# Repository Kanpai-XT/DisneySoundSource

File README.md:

# DisneySoundSource
A simple Disney Sound Source (DSS) clone based on schematics by shock__ using a CVX4 DAC by dreamblaster for audio output. The DSS provides audio out over the parallel port for a handful of games. Regardless of the CVX circuits, this device is not compatible with a Covox Speech Thing.

## Files
This repository contains the following files:
- shock__ &nbsp;&nbsp;&nbsp;&nbsp; &nbsp;&nbsp;&nbsp;&nbsp; &nbsp;&nbsp;&nbsp;&nbsp; &nbsp;&nbsp;&nbsp;&nbsp; &nbsp;&nbsp;&nbsp; subfolder conataining the original files
- dss_smd.brd &nbsp;&nbsp;&nbsp;&nbsp; &nbsp;&nbsp;&nbsp;&nbsp; &nbsp;&nbsp;&nbsp;&nbsp; &nbsp; Autodesk Eagle board file
- dd_smd.sch &nbsp;&nbsp;&nbsp;&nbsp; &nbsp;&nbsp;&nbsp;&nbsp; &nbsp;&nbsp;&nbsp;&nbsp; &nbsp;&nbsp; Autodesk Eagle schematics file
- dds_smd_bom.csv &nbsp;&nbsp;&nbsp;&nbsp; &nbsp;&nbsp; bill of materials
- dds_smd_gerber.zip &nbsp;&nbsp;&nbsp;&nbsp; Gerber files
- NE555N.ods &nbsp;&nbsp;&nbsp;&nbsp; &nbsp;&nbsp;&nbsp;&nbsp; &nbsp;&nbsp;&nbsp;&nbsp; &nbsp; spreadsheet to calculate the resistance of the trimmer R10 for a 7kHz signal 
- license.md &nbsp;&nbsp;&nbsp;&nbsp; &nbsp;&nbsp;&nbsp;&nbsp; &nbsp;&nbsp;&nbsp;&nbsp; &nbsp;&nbsp;&nbsp;&nbsp; CC-BY-NC-SA

## Gerber Files
This repository includes gerber files for PCB manufacturing. However, this PCB has plated slotted holes for the audio jack and usb jack. You are adviced to notify the manufacturer about these plated slotted holes! 

## Credits
- shock__ for the schematics and Eagle files.
- dreamblaster and Scali from VOGONS forum, for the CVX4.
- Jepael from VOGONS forum, for his input and checking over the original schematics by shock__.
- keropi from VOGONS forum, for supplying photos and measuring parts on his original DSS.
- x1541 from Verein zum Erhalt klassischer Computer e.V. (club for the preservation of classic computers) for suggesting the cheaper and non-discontinued CD40105 FIFOs.
- matze79 from DOSReloaded, for additonal circuits on the power supply.

## License
>CC-BY-NC-SA - basically do with it what you want, as long as you credit me, don't offer it commercially and make your extensions/derivates available under the same license. Only exception, you're allowed to sell PCBs created/derived from this package at a price that covers your expenses but doesn't earn you any money (I guess a $ for handling is only fair, but selling a $3 PCB for $30 would be a scumbag move and in violation of the license).

by shock__

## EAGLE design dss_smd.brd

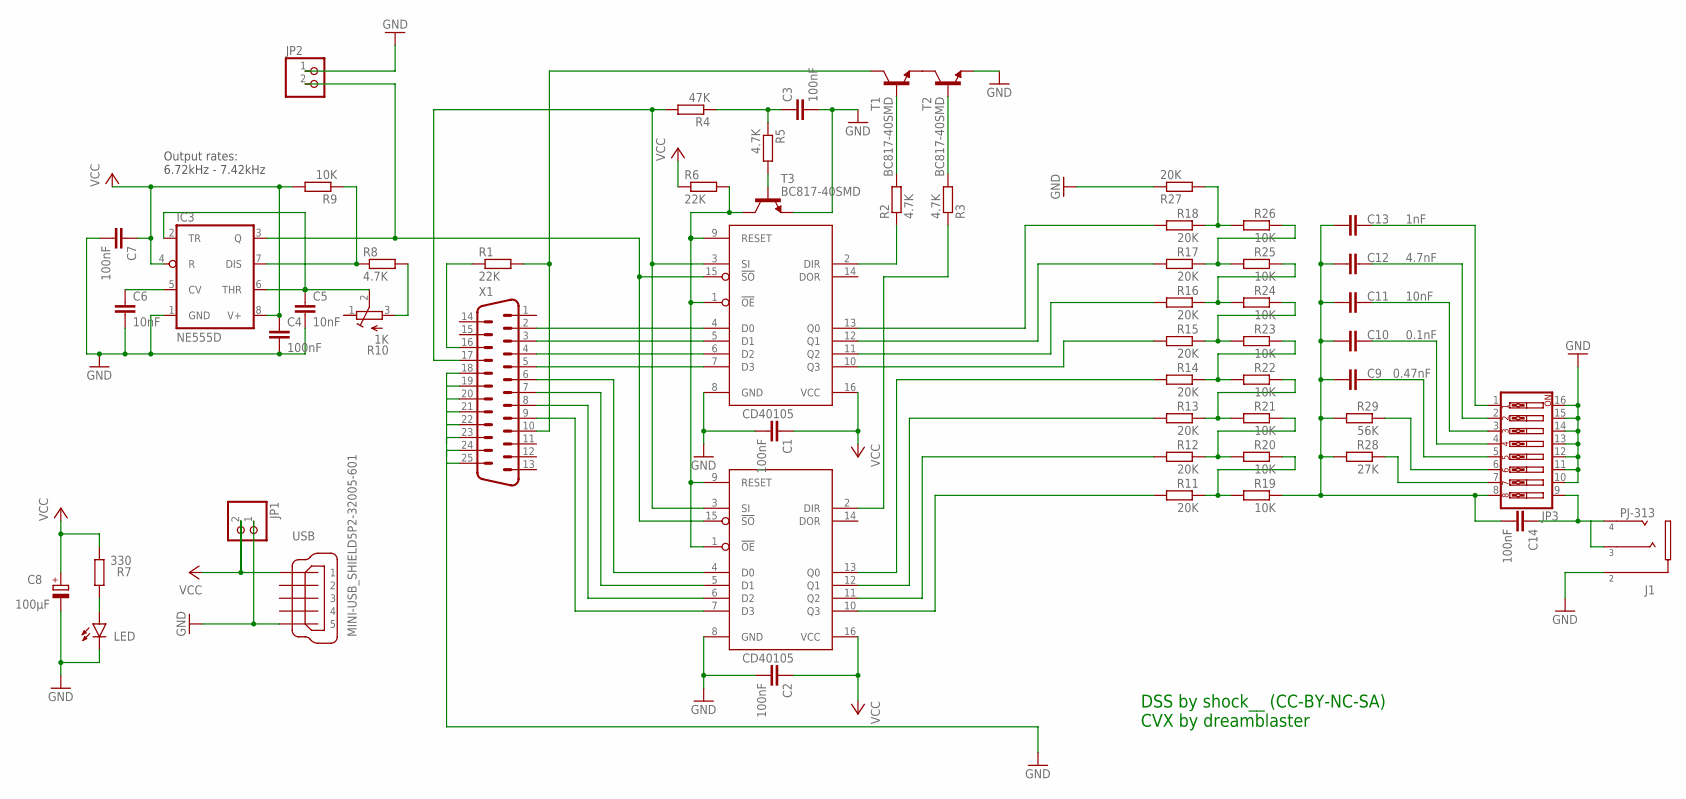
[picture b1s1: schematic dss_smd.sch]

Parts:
C1: 100nF; C0805
C2, C3, C4, C7, C14: 100nF; C0805K
C5, C6, C11: 10nF; C0805K
C8: 100µF; PANASONIC_B
C9: 0.47nF; C0805K
C10: 0.1nF; C0805K
C12: 4.7nF; C0805K
C13: 1nF; C0805K
IC1, IC2: CD40105; DIL16
IC3: NE555D; SO08
J1: PJ-313
JP1, JP2: PINHD-1X2; 1X02
JP3: SW_DIP-8; EDG-08
LED: LEDCHIP-LED0805; CHIP-LED0805
R1, R6: 22K; R0805
R2, R3, R5, R8: 4.7K; R0805
R4: 47K; R0805
R7: 330; R0805
R9, R19, R20, R21, R22, R23, R24, R25, R26: 10K; R0805
R10: 1K; RTRIMT93YA
R11, R12, R13, R14, R15, R16, R17, R18, R27: 20K; R0805
R28: 27K; R0805
R29: 56K; R0805
T1, T2, T3: BC817-40SMD; SOT23-BEC
USB: MINI-USB_SHIELD5P2-32005-601; 32005-601
X1: HS-LU_M25K

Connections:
!FULL_1: IC1.2 (DIR), R2.1
!FULL_2: IC2.2 (DIR), R3.1
CLK_IN: IC1.3 (SI), IC2.3 (SI), R4.2, X1.17
FULL: R1.2, T1.C, X1.10
GND: C1.2, C2.2, C3.2, C4.2, C5.2, C6.2, C7.2, C8.-, IC1.8 (GND), IC2.8 (GND), IC3.1 (GND), J1.2_1 (2), J1.2_2 (2), JP1.1, JP2.1, JP3.10, JP3.11, JP3.12, JP3.13, JP3.14, JP3.15, JP3.16, LED.C, R27.1, T2.E, T3.E, USB.5, X1.24, X1.25
unnamed: IC1.4 (D0), X1.2
unnamed: IC1.5 (D1), X1.3
unnamed: IC1.6 (D2), X1.4
unnamed: IC1.7 (D3), X1.5
unnamed: IC2.4 (D0), X1.6
unnamed: IC2.5 (D1), X1.7
unnamed: IC2.6 (D2), X1.8
unnamed: IC2.7 (D3), X1.9
unnamed: IC1.12 (Q1), R17.2
unnamed: IC1.11 (Q2), R16.2
unnamed: IC1.10 (Q3), R15.2
unnamed: IC2.13 (Q0), R14.2
unnamed: IC2.12 (Q1), R13.2
unnamed: IC2.11 (Q2), R12.2
unnamed: IC2.10 (Q3), R11.2
unnamed: IC1.15 (!SO), IC2.15 (!SO), IC3.3 (Q), JP2.2
unnamed: C6.1, IC3.5 (CV)
unnamed: R1.1, X1.16
unnamed: IC3.7 (DIS), R8.1, R9.1
unnamed: C5.1, IC3.2 (TR), IC3.6 (THR), R10.2 (S)
unnamed: R2.2, T1.B
unnamed: R8.2, R10.3 (A)
unnamed: R3.2, T2.B
unnamed: C3.1, R4.1, R5.1
unnamed: R5.2, T3.B
unnamed: LED.A, R7.2
unnamed: T1.E, T2.C
unnamed: R18.1, R26.2, R27.2
unnamed: R17.1, R25.2, R26.1
unnamed: R16.1, R24.2, R25.1
unnamed: R15.1, R23.2, R24.1
unnamed: R14.1, R22.2, R23.1
unnamed: R13.1, R21.2, R22.1
unnamed: R12.1, R20.2, R21.1
unnamed: R11.1, R19.2, R20.1
unnamed: C9.2, C10.2, C11.2, C12.2, C13.2, C14.2, JP3.8, R19.1, R28.2, R29.2
unnamed: JP3.7, R28.1
unnamed: IC1.13 (Q0), R18.2
unnamed: C14.1, J1.3, J1.4_1 (4), J1.4_2 (4), JP3.9
unnamed: JP3.6, R29.1
unnamed: C9.1, JP3.5
unnamed: C10.1, JP3.4
unnamed: C11.1, JP3.3
unnamed: C12.1, JP3.2
unnamed: C13.1, JP3.1
RESET: IC1.1 (!OE), IC1.9 (RESET), IC2.1 (!OE), IC2.9 (RESET), R6.2, T3.C
VCC: C1.1, C2.1, C4.1, C7.1, C8.+, IC1.16 (VCC), IC2.16 (VCC), IC3.4 (R), IC3.8 (V+), JP1.2, R6.1, R7.1, R9.2, USB.1

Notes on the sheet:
Output rates: 6.72kHz - 7.42kHz
DSS by shock__ (CC-BY-NC-SA) CVX by dreamblaster

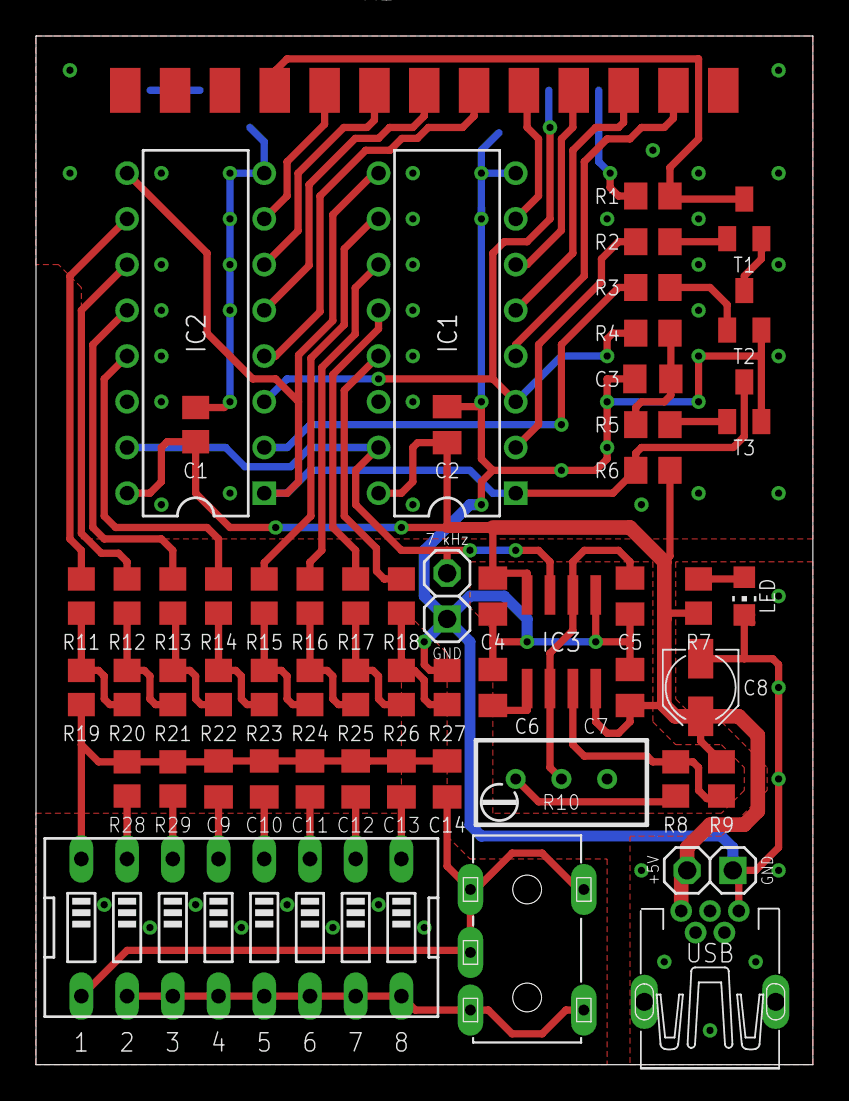
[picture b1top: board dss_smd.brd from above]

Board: 2 copper layers, 43.2 x 57.2 mm, 56 parts (0 on the bottom side), 52 nets.

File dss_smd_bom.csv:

"Qty";"Value";"Device";"Package";"Parts";"Description";"MF";"MPN";"OC_FARNELL";"OC_NEWARK";"POPULARITY";"SPICEPREFIX";
"1";"";"HS-LU_M25K";"HS-LU_M25K";"X1";"SubD-Buchse korrigiert und verschönert";"";"";"";"";"";"";
"1";"";"LEDCHIP-LED0805";"CHIP-LED0805";"LED";"LED";"";"";"";"";"68";"";
"2";"";"PINHD-1X2";"1X02";"JP1, JP2";"PIN HEADER";"";"";"";"";"98";"";
"1";"";"SW_DIP-8";"EDG-08";"JP3";"DIP SWITCH";"";"";"";"";"5";"";
"1";"0.1nF";"C-EUC0805K";"C0805K";"C10";"CAPACITOR, European symbol";"";"";"";"";"52";"C";
"1";"0.47nF";"C-EUC0805K";"C0805K";"C9";"CAPACITOR, European symbol";"";"";"";"";"52";"C";
"1";"100nF";"C-EUC0805";"C0805";"C1";"CAPACITOR, European symbol";"";"";"";"";"88";"C";
"5";"100nF";"C-EUC0805K";"C0805K";"C2, C3, C4, C7, C14";"CAPACITOR, European symbol";"";"";"";"";"52";"C";
"1";"100µF";"CPOL-EUB";"PANASONIC_B";"C8";"POLARIZED CAPACITOR, European symbol";"";"";"";"";"4";"C";
"9";"10K";"R-EU_R0805";"R0805";"R9, R19, R20, R21, R22, R23, R24, R25, R26";"RESISTOR, European symbol";"";"";"";"";"86";"R";
"3";"10nF";"C-EUC0805K";"C0805K";"C5, C6, C11";"CAPACITOR, European symbol";"";"";"";"";"52";"C";
"1";"1K";"R-TRIMMT93YA";"RTRIMT93YA";"R10";"Trimm resistor";"";"";"";"";"";"";
"1";"1nF";"C-EUC0805K";"C0805K";"C13";"CAPACITOR, European symbol";"";"";"";"";"52";"C";
"9";"20K";"R-EU_R0805";"R0805";"R11, R12, R13, R14, R15, R16, R17, R18, R27";"RESISTOR, European symbol";"";"";"";"";"86";"R";
"2";"22K";"R-EU_R0805";"R0805";"R1, R6";"RESISTOR, European symbol";"";"";"";"";"86";"R";
"1";"27K";"R-EU_R0805";"R0805";"R28";"RESISTOR, European symbol";"";"";"";"";"86";"R";
"1";"330";"R-EU_R0805";"R0805";"R7";"RESISTOR, European symbol";"";"";"";"";"86";"R";
"4";"4.7K";"R-EU_R0805";"R0805";"R2, R3, R5, R8";"RESISTOR, European symbol";"";"";"";"";"86";"R";
"1";"4.7nF";"C-EUC0805K";"C0805K";"C12";"CAPACITOR, European symbol";"";"";"";"";"52";"C";
"1";"47K";"R-EU_R0805";"R0805";"R4";"RESISTOR, European symbol";"";"";"";"";"86";"R";
"1";"56K";"R-EU_R0805";"R0805";"R29";"RESISTOR, European symbol";"";"";"";"";"86";"R";
"3";"BC817-40SMD";"BC817-40SMD";"SOT23-BEC";"T1, T2, T3";"NPN Transistor";"";"";"";"";"0";"";
"2";"CD40105";"CD40105";"DIL16";"IC1, IC2";"CD40105 16 x 4 bit FIFO";"";"";"";"";"";"";
"1";"MINI-USB_SHIELD5P2-32005-601";"MINI-USB_SHIELD5P2-32005-601";"32005-601";"USB";"MINI USB-B R/A DIP 5pol.";"";"";"unknown";"unknown";"5";"";
"1";"NE555D";"NE555D";"SO08";"IC3";"TIMER";"";"";"";"";"31";"";
"1";"PJ-313";"PJ-313";"PJ-313";"J1";"3.5mm jackdescriptionBrover Geldrop MK";"";"";"";"";"";"";

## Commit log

2022-12-01 Create gitkeep
2022-12-01 Add files via upload
    Original schematics and eagle files by shock__ under CC-BY-NC-SA
2022-12-01 Create License
